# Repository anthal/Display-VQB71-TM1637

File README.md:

# Hardware
Leiterplatte mit 1x TM1637 (Display-Treiber-IC) und 6x VQB71 (rote DDR 7-Segment Displays)

# Anwendungen
## MQTT bzw. Uhrzeit ohne Programmierung
Verwendung der [Tasmota](https://tasmota.github.io/docs/)-Firmware mit ESP8266 oder ESP32 und Anbindung an MQTT.

Tasmota Doku zum TM1637 Display-Treiber: https://tasmota.github.io/docs/TM163x/

### Anschluss bei Verwendung der **WEMOS D1** Hardware
Die 4 Pins der Display Platine können direkt 1:1 mit der **WEMOS D1** Hardware verbunden werden.
 
| WEMOS D1 mini | Display-Platine |
| ------------- | ------------- |
| 5V | VCC  |
| G | GND  | 
| D4 | DIO  | 
| D3 | CLK  | 

### Installation und Konfiguration der Firmware:
* Installation der Firmware "Tasmota Display" am einfachsten über den Chrom-Browser und https://tasmota.github.io/install/
* Configuration / Module type (Sonpoff Basic): **Generic (18)**
* D3 GPIO0: TM1637 CLK
* D4 GPIO0: TM1637 DIO

### Konfiguration der Display Parameter über die Console von Tasmota
#### Anzeige der Uhrzeit
Kommandos in der Console zu Anzeige der Uhrzeit:
```
power 1
displaymodel 15
displaywidth 6
displaytype 0
displaymode 1
displaydimmer 7
```

#### Anzeige eines Strings
Kommandos in der Console zu Anzeige eines MQTT Wertes:
```
power 1
displaymodel 15
displaywidth 6
displaytype 0
displaymode 0
displaydimmer 7
displaytext Hallo
```

#### Anzeige eines MQTT Wertes
Kommandos in der Console zu Anzeige eines MQTT Wertes:
```
power 1
displaymodel 15
displaywidth 6
displaytype 0
displaymode 0
displaydimmer 7
```
* ToDo

## Mit Programmierung
### Software
Software für Raspberry Pi Pico in MicroPython

# Bilder

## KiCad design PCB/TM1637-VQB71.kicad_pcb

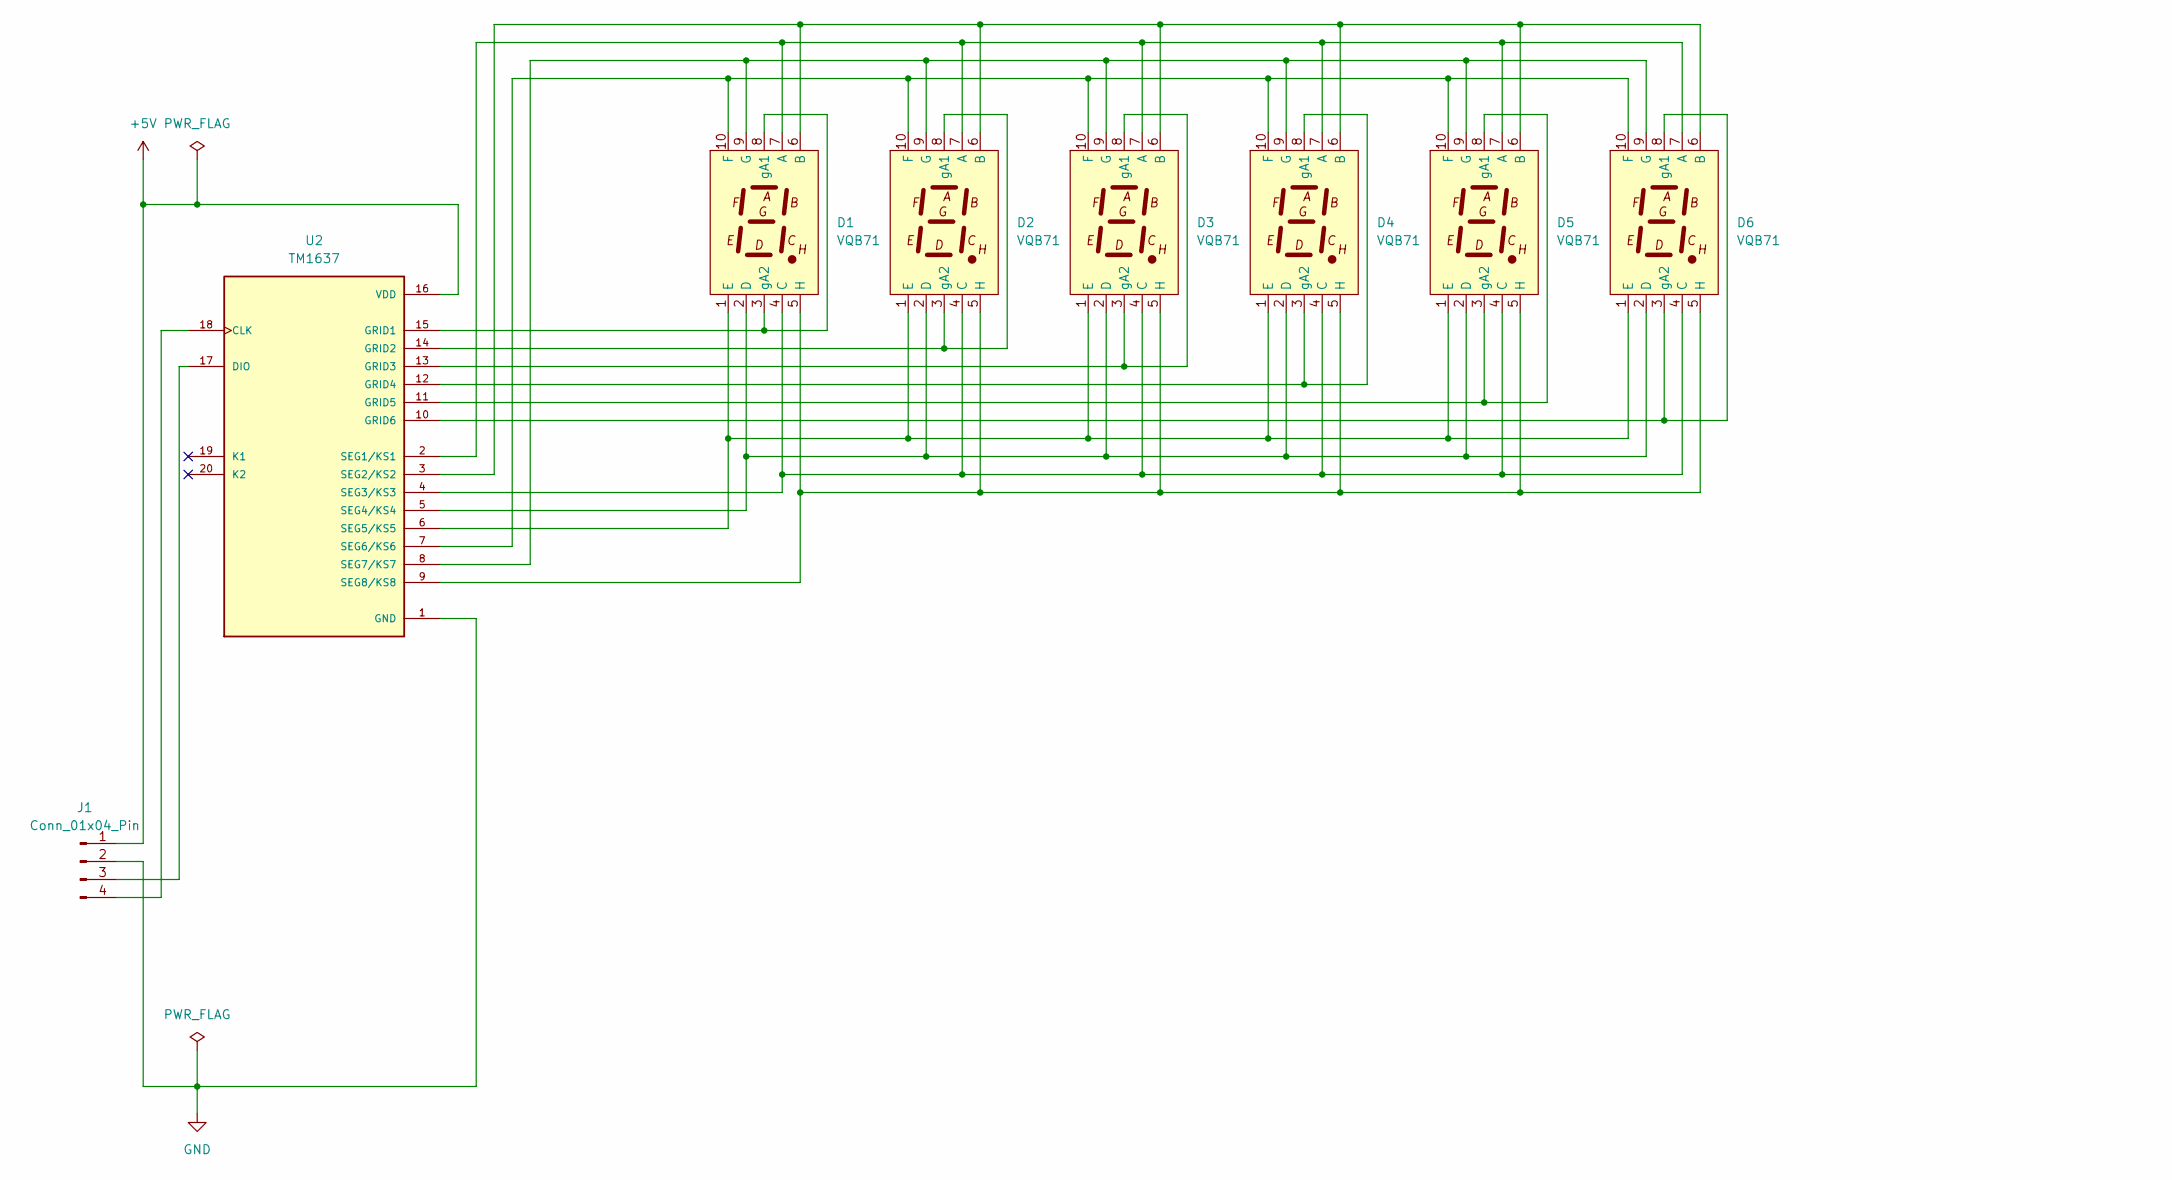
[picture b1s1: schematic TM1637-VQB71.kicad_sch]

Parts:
D1, D2, D3, D4, D5, D6: VQB71; D_VQB71
J1: Conn_01x04_Pin; PinHeader_1x04_P2.54mm_Vertical
U2: TM1637; SOP-20_7.5x12.8mm_P1.27mm; PARTREV v2.5

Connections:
+5V: J1.1, U2.16 (VDD)
GND: J1.2, U2.1 (GND)
unnamed: D1.7 (A), D2.7 (A), D3.7 (A), D4.7 (A), D5.7 (A), D6.7 (A), U2.2 (SEG1/KS1)
unnamed: D1.6 (B), D2.6 (B), D3.6 (B), D4.6 (B), D5.6 (B), D6.6 (B), U2.3 (SEG2/KS2)
unnamed: D1.4 (C), D2.4 (C), D3.4 (C), D4.4 (C), D5.4 (C), D6.4 (C), U2.4 (SEG3/KS3)
unnamed: D1.2 (D), D2.2 (D), D3.2 (D), D4.2 (D), D5.2 (D), D6.2 (D), U2.5 (SEG4/KS4)
unnamed: D1.1 (E), D2.1 (E), D3.1 (E), D4.1 (E), D5.1 (E), D6.1 (E), U2.6 (SEG5/KS5)
unnamed: D1.10 (F), D2.10 (F), D3.10 (F), D4.10 (F), D5.10 (F), D6.10 (F), U2.7 (SEG6/KS6)
unnamed: D1.9 (G), D2.9 (G), D3.9 (G), D4.9 (G), D5.9 (G), D6.9 (G), U2.8 (SEG7/KS7)
unnamed: D1.5 (H), D2.5 (H), D3.5 (H), D4.5 (H), D5.5 (H), D6.5 (H), U2.9 (SEG8/KS8)
unnamed: D1.3 (gA2), D1.8 (gA1), U2.15 (GRID1)
unnamed: D2.3 (gA2), D2.8 (gA1), U2.14 (GRID2)
unnamed: D3.3 (gA2), D3.8 (gA1), U2.13 (GRID3)
unnamed: D4.3 (gA2), D4.8 (gA1), U2.12 (GRID4)
unnamed: D5.3 (gA2), D5.8 (gA1), U2.11 (GRID5)
unnamed: D6.3 (gA2), D6.8 (gA1), U2.10 (GRID6)
unnamed: J1.3, U2.17 (DIO)
unnamed: J1.4, U2.18 (CLK)

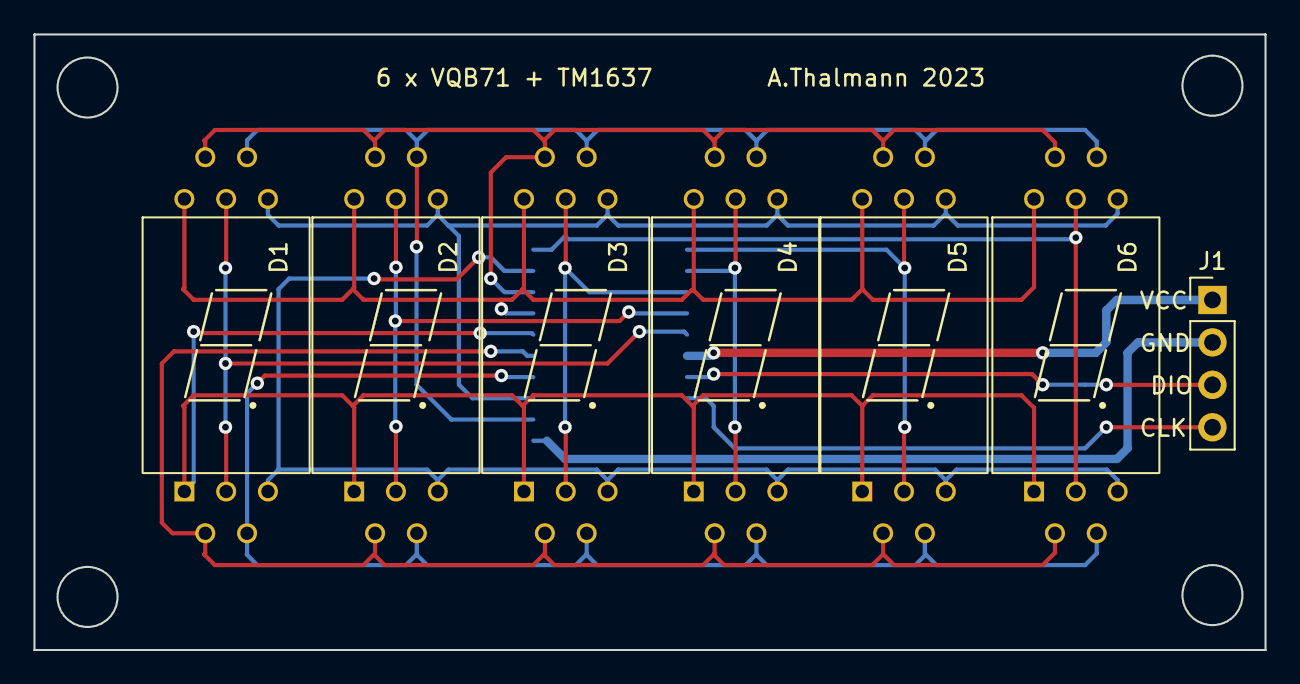
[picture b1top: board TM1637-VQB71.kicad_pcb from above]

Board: 2 copper layers, 73.7 x 36.8 mm, 8 parts (1 on the bottom side), 18 nets.

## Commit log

2023-08-21 Create PCB
2023-08-21 Add main PCB Files
2023-08-21 Add production files
2023-08-21 ADD MicroPython files
2023-08-21 CHG README file
2023-08-21 ADD PCB picture files
2023-08-21 ADD Bild in readme
2023-08-21 ADD 2. Bild in readme
2023-08-21 ADD Bilder der fertigen Leiterplatten
2023-08-21 ADD Bild in readme Datei
2023-09-12 ADD: Initialer Commit für WizFi360-EVB-Pico
